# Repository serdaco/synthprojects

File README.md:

Synthprojects
=============

Some synth projects, using arduino

Bicycle drummer
===============

Uses an arduino nano, a dreamblaster s1 synth module, and a battery powered speaker :  It plays a rock drum pattern, synchronized to the tempo of the bicycle wheel. 

How it works : the Arduino measures the period of the reed switch pulse, and adjusts the tempo of a drum sequence accordingly.  This drum sequence is sent by TTL level midi commands to a dreamblaster S1 module. The S1 is a low power waveblaster compatible module, it normally uses 5V but can be powered with 9V just as well. If the cycle period grows longer than 5 seconds, the sequence is stopped. As soon as a new period is detected the sequence is started and/or the tempo is adjusted. 

Drone Beat
===============

Arduino example code : drum and bass sequence with potmeter resonant filter control 

Arduino Nano Dreamblaster S1 hardware shield
===============

Kicad project files for the Arduino Nano shield from http://www.serdashop.com/ArduinoNanoSynthShield
The Kicad project uses the excellent component library from Walter Lain : http://www.smisioto.eu/elettronica/kicad/kicad-en.htm

MIDI Clock drum
=================
Test program for DBSHIELD1 : arduino shield for DreamBlaster X2,S2,.. on arduino UNO :
see https://www.serdashop.com/DBSHIELD1 for this shield.
MIDI Clock drum usage :  connect a midi signal with MIDI Clock to the midi input, the DBSHIELD1 will play a drum beat in sync with the incoming clock.

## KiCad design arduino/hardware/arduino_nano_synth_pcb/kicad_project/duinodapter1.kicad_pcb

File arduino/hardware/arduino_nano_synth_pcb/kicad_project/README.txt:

duinodapter1 : s1 arduino nano shield pcb :
(c)2014 Serge Defever
This project is published under creative commons 3.0 license

The project gratefully uses the excellent kicad libraries from : 
http://www.smisioto.eu/elettronica/kicad/kicad-en.htm

If you wish to order parts and/or pcb's, check this site : http://www.serdashop.com/ArduinoNanoSynthShield

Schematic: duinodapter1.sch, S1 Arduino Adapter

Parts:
C1: 10uF
C2: 100nF
C3: CAP
J1: ARDUINO_NANO_HEADER
J2: WAVEBLASTER_13X2
J3: JACK_3.5MM_3PIN
J4: HEADER_4
J5: HEADER_2
J6: HEADER_5
J7, J8, J9: HEADER_3
L1: FILTER
R1, R2, R3, R4: 10k
R5: 1k (option)
R6: 1k Option
SW1, SW2, SW3, SW4: SW_PUSH
U1: TCM809

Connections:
+12V: J2.18, J4.1
-12V: J2.22, J4.2
/agnd: J2.15, J2.17, J2.19, J2.21, J2.23, J2.25, J3.1, L1.2
/reset WAV: J2.26, R5.2, R6.2, U1.2 (~RST)
ANALOG_IN2: J1.21, J7.2
ANALOG_IN3: J1.22, J8.2
ANALOG_IN4: J1.23, J9.2
GND: C1.2, C2.2, C3.2, J1.4, J1.29, J2.1, J2.3, J2.5, J2.7, J2.9, J2.11, J4.4, J5.2, J7.1, J8.1, J9.1, L1.1, R1.2, R2.2, R3.2, R4.2, U1.3 (VDD)
INPUT2: J1.5, J6.2, R1.1, SW1.2
INPUT3: J1.6, J6.3, R2.1, SW2.2
INPUT4: J1.7, J6.4, R3.1, SW3.2
INPUT5: J1.8, J6.5, R4.1, SW4.2
unnamed: J2.24, J3.3
unnamed: J2.20, J3.2
unnamed: J1.1, J2.4
OUTPUT6: J1.9, R6.1
VCC: C1.1, C2.1, C3.1, J1.27, J2.6, J2.10, J2.14, J4.3, J6.1, J7.3, J8.3, J9.3, R5.1, SW1.1, SW2.1, SW3.1, SW4.1, U1.1 (VSS)
Vin: J1.30, J5.1

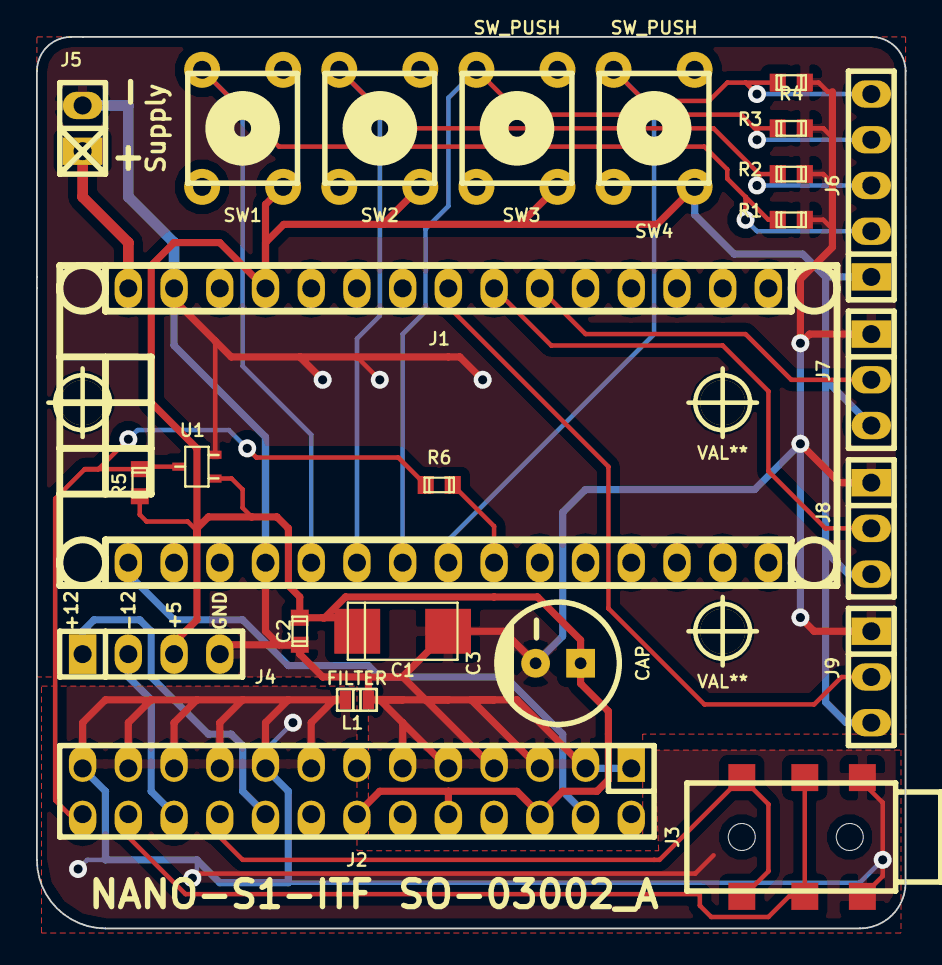
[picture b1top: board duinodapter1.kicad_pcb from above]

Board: 2 copper layers, 48.3 x 49.5 mm, 27 parts (0 on the bottom side), 18 nets.

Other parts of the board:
hole_2mm5, hole_2mm5#2, hole_2mm5#3: VAL**; hole_2mm5

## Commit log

2014-05-31 Bicycle drummer 0.1
    Bicycle drummer : uses an arduino nano, a dreamblaster s1 synth module,
    and a battery powered speaker to create a Bicycle drummer. It plays a
    rock drum pattern, synchronized to the tempo of the bicycle wheel. The
    Arduino measures the period of the reed switch pulse, and adjusts the
    tempo of a drum sequence accordingly. If the period grows longer than 5
    seconds, the sequence is stopped.
2014-05-31 Create gh-pages branch via GitHub
2014-07-25 Bicycle Drummer 0.4 // S1 Seq
    added support for Bass line sequences, synth sequences,
    manual button control. Uses Button library.
2014-07-25 S1 Arduino Nano Interface with buttons, hardware description rev A
    Moved files, added S1 Arduino Nano Interface with buttons, hardware
    description rev A
2014-07-26 Drone Beat Software Sample
    example of using the S1 with low pass resonant filter control.
    Potmeter attached to adc input.
2014-07-26 Added kicad project duinodapter1 : Waveblaster adapter for arduino nano
    This project has been tested with Dreamblaster S1.
2014-07-26 duinodapter S1 synth adapter : kicad libraries for components
    added missing lib files for kicad project
2014-07-26 lib usage explanation
2014-07-26 Changed URL for Walter's kicad component library
    the new url is
    http://www.smisioto.eu/elettronica/kicad/kicad-en.htm
2014-07-26 PS2 KEYBOARD Controlled Drum
    test program for PS2 keyboard controlled drums
2014-07-26 PS2 Keyboard : added missing return statements
2014-07-27 PS2 keyboard drum : updated sketch + modified arduino libs,
    implemented key release handling, modified lib,
    implemented patch change,...
2014-07-27 PS2KeySynth : implemented 2nd pot : filter resonance control
    Bass Line filter resonance control with 2nd potentiometer
2014-07-27 Implemented bass line instrument selection
    Using '+' and '-' keys, you can select the instrument used in the bass
    line.
2019-02-09 Added MIDICLOCKDRUM, first test version. Test program for DBSHIELD1 : arduino shield for DreamBlaster X2,S2,.. see https://www.serdashop.com/DBSHIELD1 Demo program usage : connect a midi signal with 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
2019-02-09 Added MIDI Clock drum information to readme
